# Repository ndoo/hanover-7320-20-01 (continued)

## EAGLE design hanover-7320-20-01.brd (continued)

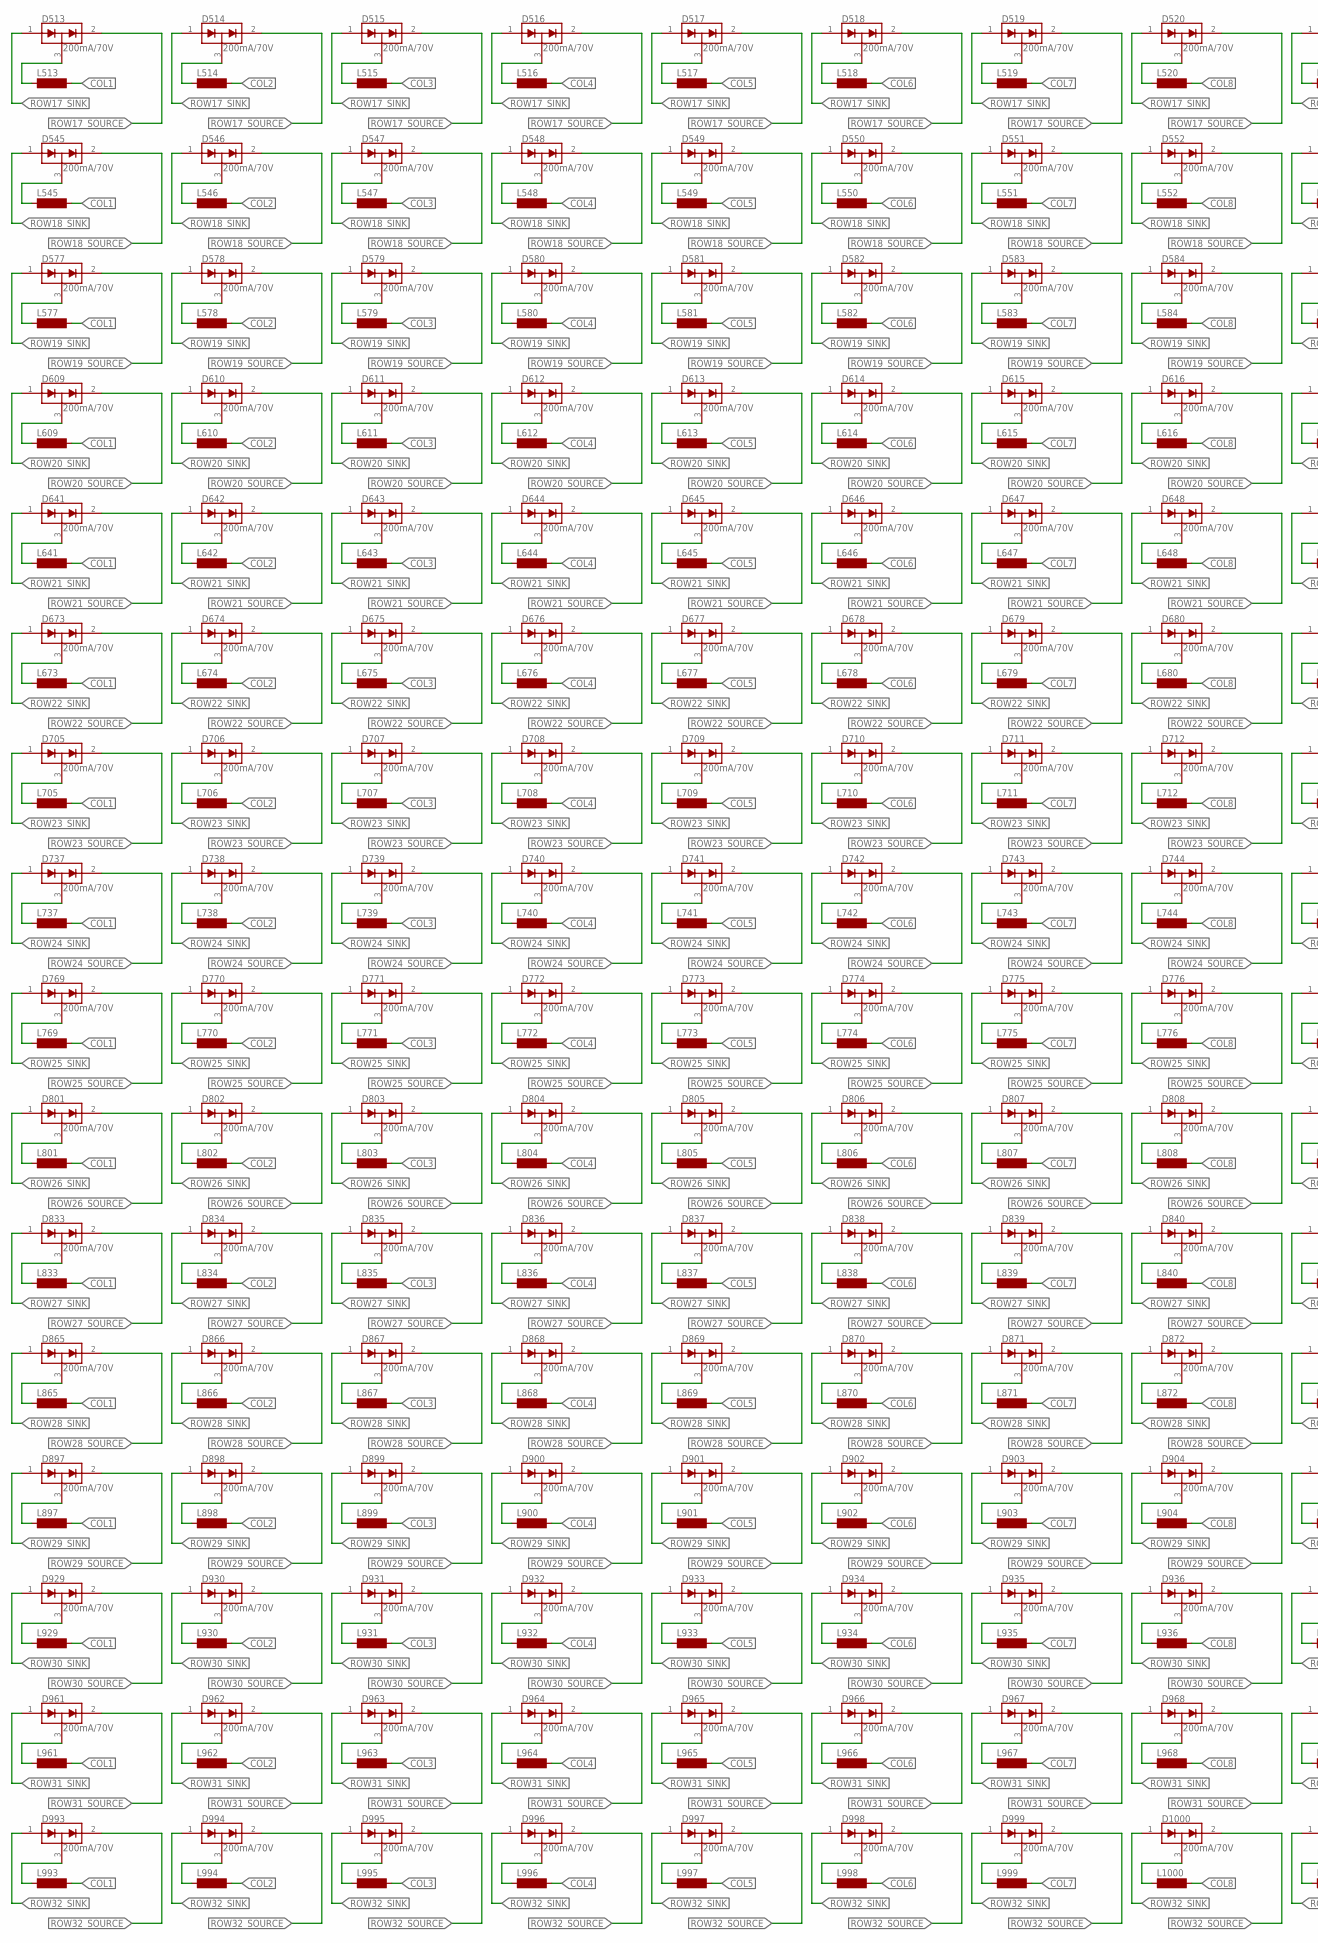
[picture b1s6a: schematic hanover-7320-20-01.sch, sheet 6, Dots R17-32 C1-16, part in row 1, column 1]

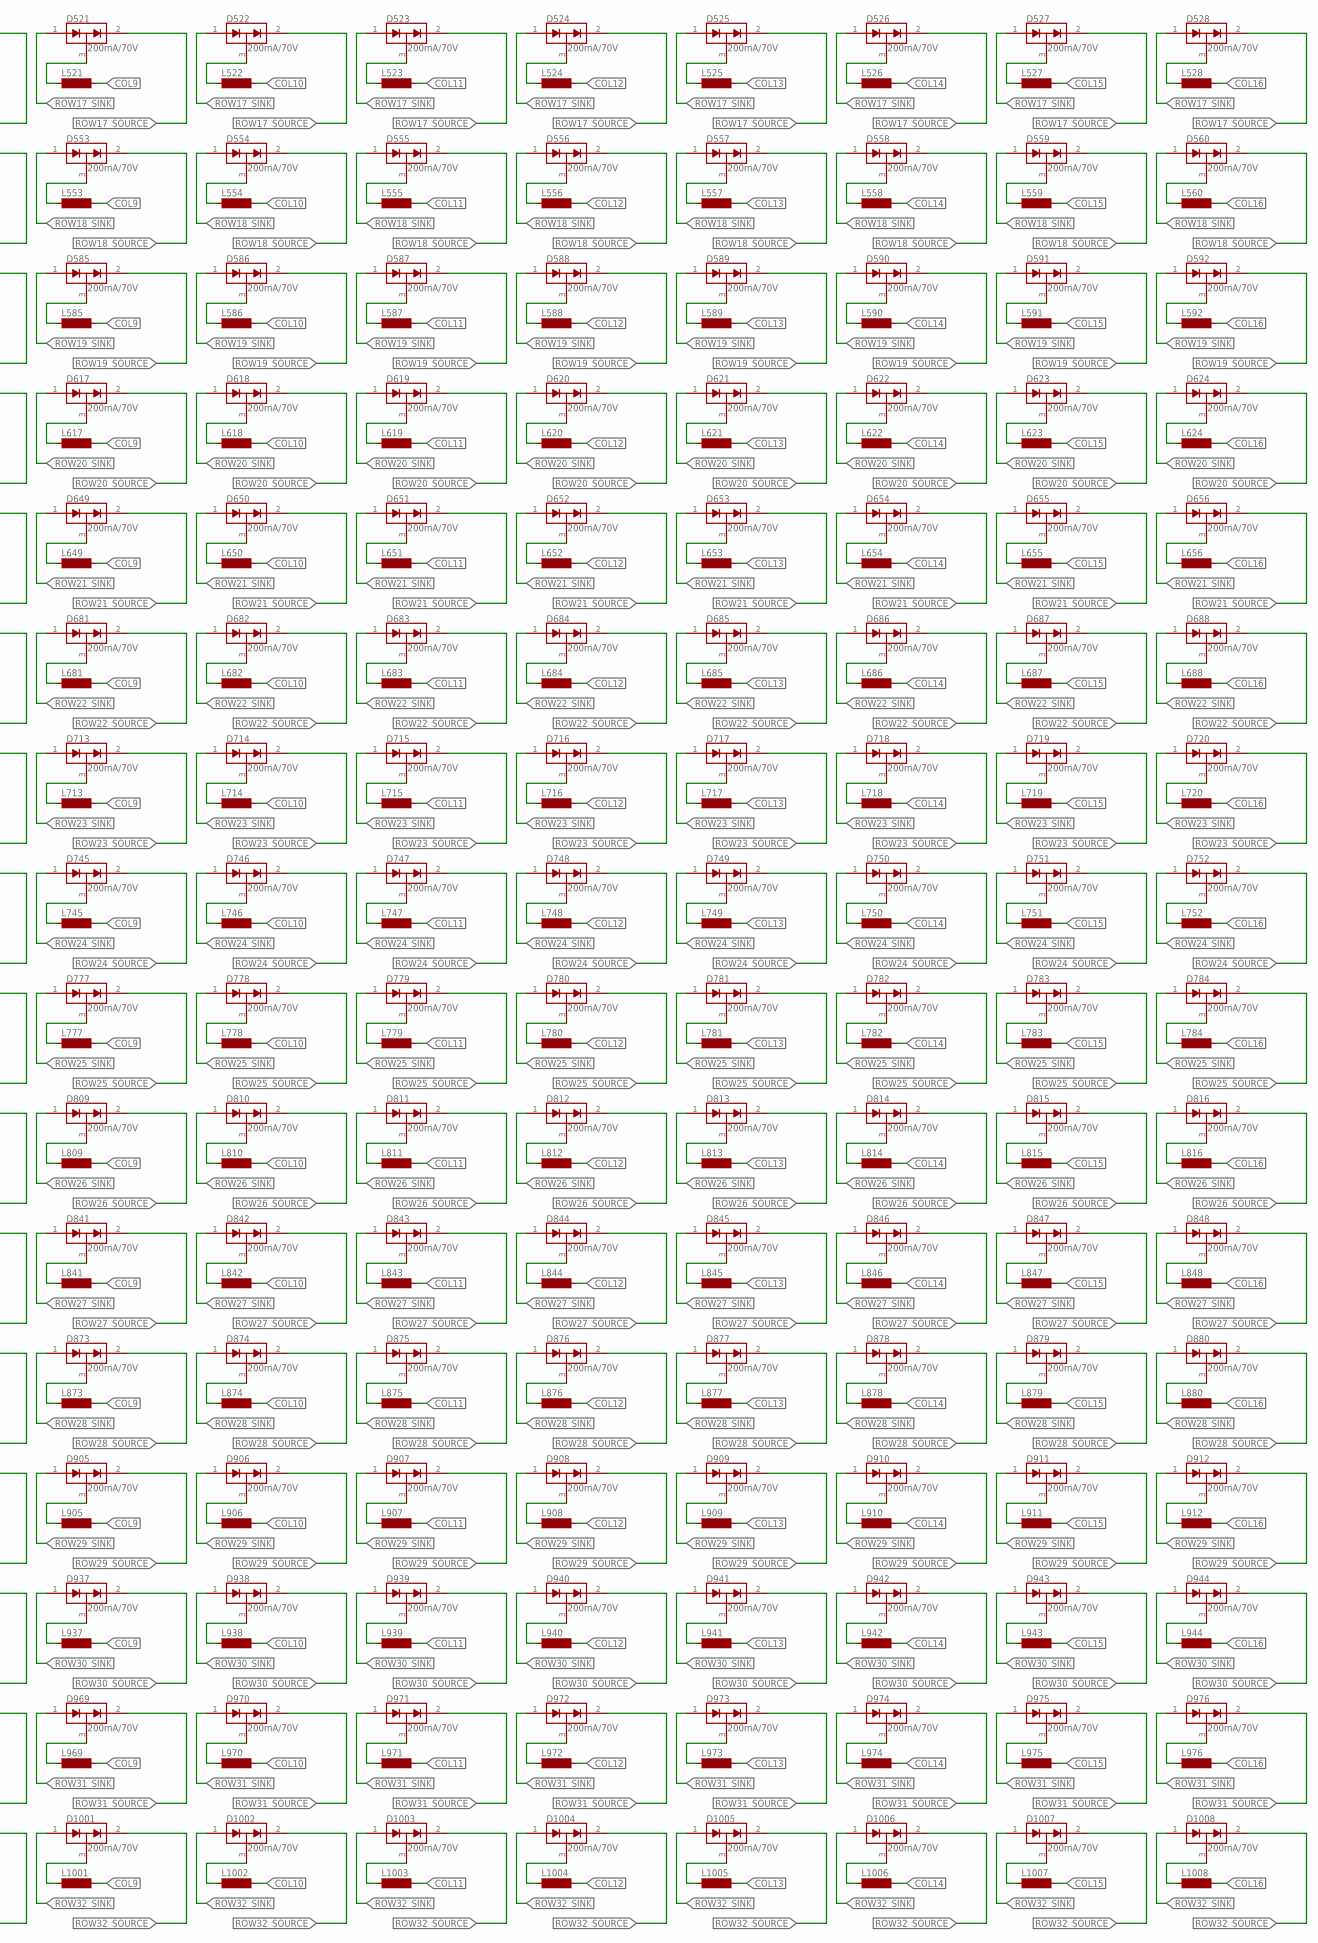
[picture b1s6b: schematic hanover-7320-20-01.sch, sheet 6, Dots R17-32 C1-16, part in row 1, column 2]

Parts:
D513, D514, D515, D516, D517, D518, D519, D520, D521, D522, D523, D524, D525, D526, D527, D528, D545, D546, D547, D548, D549, D550, D551, D552, D553, D554, D555, D556, D557, D558, D559, D560, D577, D578, D579, D580, D581, D582, D583, D584, D585, D586, D587, D588, D589, D590, D591, D592, D609, D610, D611, D612, D613, D614, D615, D616, D617, D618, D619, D620, D621, D622, D623, D624, D641, D642, D643, D644, D645, D646, D647, D648, D649, D650, D651, D652, D653, D654, D655, D656, D673, D674, D675, D676, D677, D678, D679, D680, D681, D682, D683, D684, D685, D686, D687, D688, D705, D706, D707, D708, D709, D710, D711, D712, D713, D714, D715, D716, D717, D718, D719, D720, D737, D738, D739, D740, D741, D742, D743, D744, D745, D746, D747, D748, D749, D750, D751, D752, D769, D770, D771, D772, D773, D774, D775, D776, D777, D778, D779, D780, D781, D782, D783, D784, D801, D802, D803, D804, D805, D806, D807, D808, D809, D810, D811, D812, D813, D814, D815, D816, D833, D834, D835, D836, D837, D838, D839, D840, D841, D842, D843, D844, D845, D846, D847, D848, D865, D866, D867, D868, D869, D870, D871, D872, D873, D874, D875, D876, D877, D878, D879, D880, D897, D898, D899, D900, D901, D902, D903, D904, D905, D906, D907, D908, D909, D910, D911, D912, D929, D930, D931, D932, D933, D934, D935, D936, D937, D938, D939, D940, D941, D942, D943, D944, D961, D962, D963, D964, D965, D966, D967, D968, D969, D970, D971, D972, D973, D974, D975, D976, D993, D994, D995, D996, D997, D998, D999, D1000, D1001, D1002, D1003, D1004, D1005, D1006, D1007, D1008: 200mA/70V; SOT23-3
L513, L514, L515, L516, L517, L518, L519, L520, L521, L522, L523, L524, L525, L526, L527, L528, L545, L546, L547, L548, L549, L550, L551, L552, L553, L554, L555, L556, L557, L558, L559, L560, L577, L578, L579, L580, L581, L582, L583, L584, L585, L586, L587, L588, L589, L590, L591, L592, L609, L610, L611, L612, L613, L614, L615, L616, L617, L618, L619, L620, L621, L622, L623, L624, L641, L642, L643, L644, L645, L646, L647, L648, L649, L650, L651, L652, L653, L654, L655, L656, L673, L674, L675, L676, L677, L678, L679, L680, L681, L682, L683, L684, L685, L686, L687, L688, L705, L706, L707, L708, L709, L710, L711, L712, L713, L714, L715, L716, L717, L718, L719, L720, L737, L738, L739, L740, L741, L742, L743, L744, L745, L746, L747, L748, L749, L750, L751, L752, L769, L770, L771, L772, L773, L774, L775, L776, L777, L778, L779, L780, L781, L782, L783, L784, L801, L802, L803, L804, L805, L806, L807, L808, L809, L810, L811, L812, L813, L814, L815, L816, L833, L834, L835, L836, L837, L838, L839, L840, L841, L842, L843, L844, L845, L846, L847, L848, L865, L866, L867, L868, L869, L870, L871, L872, L873, L874, L875, L876, L877, L878, L879, L880, L897, L898, L899, L900, L901, L902, L903, L904, L905, L906, L907, L908, L909, L910, L911, L912, L929, L930, L931, L932, L933, L934, L935, L936, L937, L938, L939, L940, L941, L942, L943, L944, L961, L962, L963, L964, L965, L966, L967, L968, L969, L970, L971, L972, L973, L974, L975, L976, L993, L994, L995, L996, L997, L998, L999, L1000, L1001, L1002, L1003, L1004, L1005, L1006, L1007, L1008: SD8

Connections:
COL1: L513.2, L545.2, L577.2, L609.2, L641.2, L673.2, L705.2, L737.2, L769.2, L801.2, L833.2, L865.2, L897.2, L929.2, L961.2, L993.2; also elsewhere on the board
COL2: L514.2, L546.2, L578.2, L610.2, L642.2, L674.2, L706.2, L738.2, L770.2, L802.2, L834.2, L866.2, L898.2, L930.2, L962.2, L994.2; also elsewhere on the board
COL3: L515.2, L547.2, L579.2, L611.2, L643.2, L675.2, L707.2, L739.2, L771.2, L803.2, L835.2, L867.2, L899.2, L931.2, L963.2, L995.2; also elsewhere on the board
COL4: L516.2, L548.2, L580.2, L612.2, L644.2, L676.2, L708.2, L740.2, L772.2, L804.2, L836.2, L868.2, L900.2, L932.2, L964.2, L996.2; also elsewhere on the board
COL5: L517.2, L549.2, L581.2, L613.2, L645.2, L677.2, L709.2, L741.2, L773.2, L805.2, L837.2, L869.2, L901.2, L933.2, L965.2, L997.2; also elsewhere on the board
COL6: L518.2, L550.2, L582.2, L614.2, L646.2, L678.2, L710.2, L742.2, L774.2, L806.2, L838.2, L870.2, L902.2, L934.2, L966.2, L998.2; also elsewhere on the board
COL7: L519.2, L551.2, L583.2, L615.2, L647.2, L679.2, L711.2, L743.2, L775.2, L807.2, L839.2, L871.2, L903.2, L935.2, L967.2, L999.2; also elsewhere on the board
COL8: L520.2, L552.2, L584.2, L616.2, L648.2, L680.2, L712.2, L744.2, L776.2, L808.2, L840.2, L872.2, L904.2, L936.2, L968.2, L1000.2; also elsewhere on the board
COL9: L521.2, L553.2, L585.2, L617.2, L649.2, L681.2, L713.2, L745.2, L777.2, L809.2, L841.2, L873.2, L905.2, L937.2, L969.2, L1001.2; also elsewhere on the board
COL10: L522.2, L554.2, L586.2, L618.2, L650.2, L682.2, L714.2, L746.2, L778.2, L810.2, L842.2, L874.2, L906.2, L938.2, L970.2, L1002.2; also elsewhere on the board
COL11: L523.2, L555.2, L587.2, L619.2, L651.2, L683.2, L715.2, L747.2, L779.2, L811.2, L843.2, L875.2, L907.2, L939.2, L971.2, L1003.2; also elsewhere on the board
COL12: L524.2, L556.2, L588.2, L620.2, L652.2, L684.2, L716.2, L748.2, L780.2, L812.2, L844.2, L876.2, L908.2, L940.2, L972.2, L1004.2; also elsewhere on the board
COL13: L525.2, L557.2, L589.2, L621.2, L653.2, L685.2, L717.2, L749.2, L781.2, L813.2, L845.2, L877.2, L909.2, L941.2, L973.2, L1005.2; also elsewhere on the board
COL14: L526.2, L558.2, L590.2, L622.2, L654.2, L686.2, L718.2, L750.2, L782.2, L814.2, L846.2, L878.2, L910.2, L942.2, L974.2, L1006.2; also elsewhere on the board
COL15: L527.2, L559.2, L591.2, L623.2, L655.2, L687.2, L719.2, L751.2, L783.2, L815.2, L847.2, L879.2, L911.2, L943.2, L975.2, L1007.2; also elsewhere on the board
COL16: L528.2, L560.2, L592.2, L624.2, L656.2, L688.2, L720.2, L752.2, L784.2, L816.2, L848.2, L880.2, L912.2, L944.2, L976.2, L1008.2; also elsewhere on the board
unnamed: D513.3 (COM), L513.1
unnamed: D514.3 (COM), L514.1
unnamed: D515.3 (COM), L515.1
unnamed: D516.3 (COM), L516.1
unnamed: D517.3 (COM), L517.1
unnamed: D518.3 (COM), L518.1
unnamed: D519.3 (COM), L519.1
unnamed: D520.3 (COM), L520.1
unnamed: D521.3 (COM), L521.1
unnamed: D522.3 (COM), L522.1
unnamed: D523.3 (COM), L523.1
unnamed: D524.3 (COM), L524.1
unnamed: D525.3 (COM), L525.1
unnamed: D526.3 (COM), L526.1
unnamed: D527.3 (COM), L527.1
unnamed: D528.3 (COM), L528.1
unnamed: D545.3 (COM), L545.1
unnamed: D546.3 (COM), L546.1
unnamed: D547.3 (COM), L547.1
unnamed: D548.3 (COM), L548.1
unnamed: D549.3 (COM), L549.1
unnamed: D550.3 (COM), L550.1
unnamed: D551.3 (COM), L551.1
unnamed: D552.3 (COM), L552.1
unnamed: D553.3 (COM), L553.1
unnamed: D554.3 (COM), L554.1
unnamed: D555.3 (COM), L555.1
unnamed: D556.3 (COM), L556.1
unnamed: D557.3 (COM), L557.1
unnamed: D558.3 (COM), L558.1
unnamed: D559.3 (COM), L559.1
unnamed: D560.3 (COM), L560.1
unnamed: D577.3 (COM), L577.1
unnamed: D578.3 (COM), L578.1
unnamed: D579.3 (COM), L579.1
unnamed: D580.3 (COM), L580.1
unnamed: D581.3 (COM), L581.1
unnamed: D582.3 (COM), L582.1
unnamed: D583.3 (COM), L583.1
unnamed: D584.3 (COM), L584.1
unnamed: D585.3 (COM), L585.1
unnamed: D586.3 (COM), L586.1
unnamed: D587.3 (COM), L587.1
unnamed: D588.3 (COM), L588.1
unnamed: D589.3 (COM), L589.1
unnamed: D590.3 (COM), L590.1
unnamed: D591.3 (COM), L591.1
unnamed: D592.3 (COM), L592.1
unnamed: D609.3 (COM), L609.1
unnamed: D610.3 (COM), L610.1
unnamed: D611.3 (COM), L611.1
unnamed: D612.3 (COM), L612.1
unnamed: D613.3 (COM), L613.1
unnamed: D614.3 (COM), L614.1
unnamed: D615.3 (COM), L615.1
unnamed: D616.3 (COM), L616.1
unnamed: D617.3 (COM), L617.1
unnamed: D618.3 (COM), L618.1
unnamed: D619.3 (COM), L619.1
unnamed: D620.3 (COM), L620.1
unnamed: D621.3 (COM), L621.1
unnamed: D622.3 (COM), L622.1
unnamed: D623.3 (COM), L623.1
unnamed: D624.3 (COM), L624.1
unnamed: D641.3 (COM), L641.1
unnamed: D642.3 (COM), L642.1
unnamed: D643.3 (COM), L643.1
unnamed: D644.3 (COM), L644.1
unnamed: D645.3 (COM), L645.1
unnamed: D646.3 (COM), L646.1
unnamed: D647.3 (COM), L647.1
unnamed: D648.3 (COM), L648.1
unnamed: D649.3 (COM), L649.1
unnamed: D650.3 (COM), L650.1
unnamed: D651.3 (COM), L651.1
unnamed: D652.3 (COM), L652.1
unnamed: D653.3 (COM), L653.1
unnamed: D654.3 (COM), L654.1
unnamed: D655.3 (COM), L655.1
unnamed: D656.3 (COM), L656.1
unnamed: D673.3 (COM), L673.1
unnamed: D674.3 (COM), L674.1
unnamed: D675.3 (COM), L675.1
unnamed: D676.3 (COM), L676.1
unnamed: D677.3 (COM), L677.1
unnamed: D678.3 (COM), L678.1
unnamed: D679.3 (COM), L679.1
unnamed: D680.3 (COM), L680.1
unnamed: D681.3 (COM), L681.1
unnamed: D682.3 (COM), L682.1
unnamed: D683.3 (COM), L683.1
unnamed: D684.3 (COM), L684.1
unnamed: D685.3 (COM), L685.1
unnamed: D686.3 (COM), L686.1
unnamed: D687.3 (COM), L687.1
unnamed: D688.3 (COM), L688.1
unnamed: D705.3 (COM), L705.1
unnamed: D706.3 (COM), L706.1
unnamed: D707.3 (COM), L707.1
unnamed: D708.3 (COM), L708.1
unnamed: D709.3 (COM), L709.1
unnamed: D710.3 (COM), L710.1
unnamed: D711.3 (COM), L711.1
unnamed: D712.3 (COM), L712.1
unnamed: D713.3 (COM), L713.1
unnamed: D714.3 (COM), L714.1
unnamed: D715.3 (COM), L715.1
unnamed: D716.3 (COM), L716.1
unnamed: D717.3 (COM), L717.1
unnamed: D718.3 (COM), L718.1
unnamed: D719.3 (COM), L719.1
unnamed: D720.3 (COM), L720.1
unnamed: D737.3 (COM), L737.1
unnamed: D738.3 (COM), L738.1
unnamed: D739.3 (COM), L739.1
unnamed: D740.3 (COM), L740.1
unnamed: D741.3 (COM), L741.1
unnamed: D742.3 (COM), L742.1
unnamed: D743.3 (COM), L743.1
unnamed: D744.3 (COM), L744.1
unnamed: D745.3 (COM), L745.1
unnamed: D746.3 (COM), L746.1
unnamed: D747.3 (COM), L747.1
unnamed: D748.3 (COM), L748.1
unnamed: D749.3 (COM), L749.1
unnamed: D750.3 (COM), L750.1
unnamed: D751.3 (COM), L751.1
unnamed: D752.3 (COM), L752.1
unnamed: D769.3 (COM), L769.1
unnamed: D770.3 (COM), L770.1
unnamed: D771.3 (COM), L771.1
unnamed: D772.3 (COM), L772.1
unnamed: D773.3 (COM), L773.1
unnamed: D774.3 (COM), L774.1
unnamed: D775.3 (COM), L775.1
unnamed: D776.3 (COM), L776.1
unnamed: D777.3 (COM), L777.1
unnamed: D778.3 (COM), L778.1
unnamed: D779.3 (COM), L779.1
unnamed: D780.3 (COM), L780.1
unnamed: D781.3 (COM), L781.1
unnamed: D782.3 (COM), L782.1
unnamed: D783.3 (COM), L783.1
unnamed: D784.3 (COM), L784.1
unnamed: D801.3 (COM), L801.1
unnamed: D802.3 (COM), L802.1
unnamed: D803.3 (COM), L803.1
unnamed: D804.3 (COM), L804.1
unnamed: D805.3 (COM), L805.1
unnamed: D806.3 (COM), L806.1
unnamed: D807.3 (COM), L807.1
unnamed: D808.3 (COM), L808.1
unnamed: D809.3 (COM), L809.1
unnamed: D810.3 (COM), L810.1
unnamed: D811.3 (COM), L811.1
unnamed: D812.3 (COM), L812.1
unnamed: D813.3 (COM), L813.1
unnamed: D814.3 (COM), L814.1
unnamed: D815.3 (COM), L815.1
unnamed: D816.3 (COM), L816.1
unnamed: D833.3 (COM), L833.1
unnamed: D834.3 (COM), L834.1
unnamed: D835.3 (COM), L835.1
unnamed: D836.3 (COM), L836.1
unnamed: D837.3 (COM), L837.1
unnamed: D838.3 (COM), L838.1
unnamed: D839.3 (COM), L839.1
unnamed: D840.3 (COM), L840.1
unnamed: D841.3 (COM), L841.1
unnamed: D842.3 (COM), L842.1
unnamed: D843.3 (COM), L843.1
unnamed: D844.3 (COM), L844.1
unnamed: D845.3 (COM), L845.1
unnamed: D846.3 (COM), L846.1
unnamed: D847.3 (COM), L847.1
unnamed: D848.3 (COM), L848.1
unnamed: D865.3 (COM), L865.1
unnamed: D866.3 (COM), L866.1
unnamed: D867.3 (COM), L867.1
unnamed: D868.3 (COM), L868.1
unnamed: D869.3 (COM), L869.1
unnamed: D870.3 (COM), L870.1
unnamed: D871.3 (COM), L871.1
unnamed: D872.3 (COM), L872.1
unnamed: D873.3 (COM), L873.1
unnamed: D874.3 (COM), L874.1
unnamed: D875.3 (COM), L875.1
unnamed: D876.3 (COM), L876.1
unnamed: D877.3 (COM), L877.1
unnamed: D878.3 (COM), L878.1
unnamed: D879.3 (COM), L879.1
unnamed: D880.3 (COM), L880.1
unnamed: D897.3 (COM), L897.1
unnamed: D898.3 (COM), L898.1
unnamed: D899.3 (COM), L899.1
unnamed: D900.3 (COM), L900.1
unnamed: D901.3 (COM), L901.1
unnamed: D902.3 (COM), L902.1
unnamed: D903.3 (COM), L903.1
unnamed: D904.3 (COM), L904.1
unnamed: D905.3 (COM), L905.1
unnamed: D906.3 (COM), L906.1
unnamed: D907.3 (COM), L907.1
unnamed: D908.3 (COM), L908.1
unnamed: D909.3 (COM), L909.1
unnamed: D910.3 (COM), L910.1
unnamed: D911.3 (COM), L911.1
unnamed: D912.3 (COM), L912.1
unnamed: D929.3 (COM), L929.1
unnamed: D930.3 (COM), L930.1
unnamed: D931.3 (COM), L931.1
unnamed: D932.3 (COM), L932.1
unnamed: D933.3 (COM), L933.1
unnamed: D934.3 (COM), L934.1
unnamed: D935.3 (COM), L935.1
unnamed: D936.3 (COM), L936.1
unnamed: D937.3 (COM), L937.1
unnamed: D938.3 (COM), L938.1
unnamed: D939.3 (COM), L939.1
unnamed: D940.3 (COM), L940.1
unnamed: D941.3 (COM), L941.1
unnamed: D942.3 (COM), L942.1
unnamed: D943.3 (COM), L943.1
unnamed: D944.3 (COM), L944.1
unnamed: D961.3 (COM), L961.1
unnamed: D962.3 (COM), L962.1
unnamed: D963.3 (COM), L963.1
unnamed: D964.3 (COM), L964.1
unnamed: D965.3 (COM), L965.1
unnamed: D966.3 (COM), L966.1
unnamed: D967.3 (COM), L967.1
unnamed: D968.3 (COM), L968.1
unnamed: D969.3 (COM), L969.1
unnamed: D970.3 (COM), L970.1
unnamed: D971.3 (COM), L971.1
unnamed: D972.3 (COM), L972.1
unnamed: D973.3 (COM), L973.1
unnamed: D974.3 (COM), L974.1
unnamed: D975.3 (COM), L975.1
unnamed: D976.3 (COM), L976.1
unnamed: D993.3 (COM), L993.1
unnamed: D994.3 (COM), L994.1
unnamed: D995.3 (COM), L995.1
unnamed: D996.3 (COM), L996.1
unnamed: D997.3 (COM), L997.1
unnamed: D998.3 (COM), L998.1
unnamed: D999.3 (COM), L999.1
unnamed: D1000.3 (COM), L1000.1
unnamed: D1001.3 (COM), L1001.1
unnamed: D1002.3 (COM), L1002.1
unnamed: D1003.3 (COM), L1003.1
unnamed: D1004.3 (COM), L1004.1
unnamed: D1005.3 (COM), L1005.1
unnamed: D1006.3 (COM), L1006.1
unnamed: D1007.3 (COM), L1007.1
unnamed: D1008.3 (COM), L1008.1
ROW17_SINK: D513.1 (A1), D514.1 (A1), D515.1 (A1), D516.1 (A1), D517.1 (A1), D518.1 (A1), D519.1 (A1), D520.1 (A1), D521.1 (A1), D522.1 (A1), D523.1 (A1), D524.1 (A1), D525.1 (A1), D526.1 (A1), D527.1 (A1), D528.1 (A1); also elsewhere on the board
ROW17_SOURCE: D513.2 (C2), D514.2 (C2), D515.2 (C2), D516.2 (C2), D517.2 (C2), D518.2 (C2), D519.2 (C2), D520.2 (C2), D521.2 (C2), D522.2 (C2), D523.2 (C2), D524.2 (C2), D525.2 (C2), D526.2 (C2), D527.2 (C2), D528.2 (C2); also elsewhere on the board
ROW18_SINK: D545.1 (A1), D546.1 (A1), D547.1 (A1), D548.1 (A1), D549.1 (A1), D550.1 (A1), D551.1 (A1), D552.1 (A1), D553.1 (A1), D554.1 (A1), D555.1 (A1), D556.1 (A1), D557.1 (A1), D558.1 (A1), D559.1 (A1), D560.1 (A1); also elsewhere on the board
ROW18_SOURCE: D545.2 (C2), D546.2 (C2), D547.2 (C2), D548.2 (C2), D549.2 (C2), D550.2 (C2), D551.2 (C2), D552.2 (C2), D553.2 (C2), D554.2 (C2), D555.2 (C2), D556.2 (C2), D557.2 (C2), D558.2 (C2), D559.2 (C2), D560.2 (C2); also elsewhere on the board
ROW19_SINK: D577.1 (A1), D578.1 (A1), D579.1 (A1), D580.1 (A1), D581.1 (A1), D582.1 (A1), D583.1 (A1), D584.1 (A1), D585.1 (A1), D586.1 (A1), D587.1 (A1), D588.1 (A1), D589.1 (A1), D590.1 (A1), D591.1 (A1), D592.1 (A1); also elsewhere on the board
ROW19_SOURCE: D577.2 (C2), D578.2 (C2), D579.2 (C2), D580.2 (C2), D581.2 (C2), D582.2 (C2), D583.2 (C2), D584.2 (C2), D585.2 (C2), D586.2 (C2), D587.2 (C2), D588.2 (C2), D589.2 (C2), D590.2 (C2), D591.2 (C2), D592.2 (C2); also elsewhere on the board
ROW20_SINK: D609.1 (A1), D610.1 (A1), D611.1 (A1), D612.1 (A1), D613.1 (A1), D614.1 (A1), D615.1 (A1), D616.1 (A1), D617.1 (A1), D618.1 (A1), D619.1 (A1), D620.1 (A1), D621.1 (A1), D622.1 (A1), D623.1 (A1), D624.1 (A1); also elsewhere on the board
ROW20_SOURCE: D609.2 (C2), D610.2 (C2), D611.2 (C2), D612.2 (C2), D613.2 (C2), D614.2 (C2), D615.2 (C2), D616.2 (C2), D617.2 (C2), D618.2 (C2), D619.2 (C2), D620.2 (C2), D621.2 (C2), D622.2 (C2), D623.2 (C2), D624.2 (C2); also elsewhere on the board
ROW21_SINK: D641.1 (A1), D642.1 (A1), D643.1 (A1), D644.1 (A1), D645.1 (A1), D646.1 (A1), D647.1 (A1), D648.1 (A1), D649.1 (A1), D650.1 (A1), D651.1 (A1), D652.1 (A1), D653.1 (A1), D654.1 (A1), D655.1 (A1), D656.1 (A1); also elsewhere on the board
ROW21_SOURCE: D641.2 (C2), D642.2 (C2), D643.2 (C2), D644.2 (C2), D645.2 (C2), D646.2 (C2), D647.2 (C2), D648.2 (C2), D649.2 (C2), D650.2 (C2), D651.2 (C2), D652.2 (C2), D653.2 (C2), D654.2 (C2), D655.2 (C2), D656.2 (C2); also elsewhere on the board
ROW22_SINK: D673.1 (A1), D674.1 (A1), D675.1 (A1), D676.1 (A1), D677.1 (A1), D678.1 (A1), D679.1 (A1), D680.1 (A1), D681.1 (A1), D682.1 (A1), D683.1 (A1), D684.1 (A1), D685.1 (A1), D686.1 (A1), D687.1 (A1), D688.1 (A1); also elsewhere on the board
ROW22_SOURCE: D673.2 (C2), D674.2 (C2), D675.2 (C2), D676.2 (C2), D677.2 (C2), D678.2 (C2), D679.2 (C2), D680.2 (C2), D681.2 (C2), D682.2 (C2), D683.2 (C2), D684.2 (C2), D685.2 (C2), D686.2 (C2), D687.2 (C2), D688.2 (C2); also elsewhere on the board
ROW23_SINK: D705.1 (A1), D706.1 (A1), D707.1 (A1), D708.1 (A1), D709.1 (A1), D710.1 (A1), D711.1 (A1), D712.1 (A1), D713.1 (A1), D714.1 (A1), D715.1 (A1), D716.1 (A1), D717.1 (A1), D718.1 (A1), D719.1 (A1), D720.1 (A1); also elsewhere on the board
ROW23_SOURCE: D705.2 (C2), D706.2 (C2), D707.2 (C2), D708.2 (C2), D709.2 (C2), D710.2 (C2), D711.2 (C2), D712.2 (C2), D713.2 (C2), D714.2 (C2), D715.2 (C2), D716.2 (C2), D717.2 (C2), D718.2 (C2), D719.2 (C2), D720.2 (C2); also elsewhere on the board
ROW24_SINK: D737.1 (A1), D738.1 (A1), D739.1 (A1), D740.1 (A1), D741.1 (A1), D742.1 (A1), D743.1 (A1), D744.1 (A1), D745.1 (A1), D746.1 (A1), D747.1 (A1), D748.1 (A1), D749.1 (A1), D750.1 (A1), D751.1 (A1), D752.1 (A1); also elsewhere on the board
ROW24_SOURCE: D737.2 (C2), D738.2 (C2), D739.2 (C2), D740.2 (C2), D741.2 (C2), D742.2 (C2), D743.2 (C2), D744.2 (C2), D745.2 (C2), D746.2 (C2), D747.2 (C2), D748.2 (C2), D749.2 (C2), D750.2 (C2), D751.2 (C2), D752.2 (C2); also elsewhere on the board
ROW25_SINK: D769.1 (A1), D770.1 (A1), D771.1 (A1), D772.1 (A1), D773.1 (A1), D774.1 (A1), D775.1 (A1), D776.1 (A1), D777.1 (A1), D778.1 (A1), D779.1 (A1), D780.1 (A1), D781.1 (A1), D782.1 (A1), D783.1 (A1), D784.1 (A1); also elsewhere on the board
ROW25_SOURCE: D769.2 (C2), D770.2 (C2), D771.2 (C2), D772.2 (C2), D773.2 (C2), D774.2 (C2), D775.2 (C2), D776.2 (C2), D777.2 (C2), D778.2 (C2), D779.2 (C2), D780.2 (C2), D781.2 (C2), D782.2 (C2), D783.2 (C2), D784.2 (C2); also elsewhere on the board
ROW26_SINK: D801.1 (A1), D802.1 (A1), D803.1 (A1), D804.1 (A1), D805.1 (A1), D806.1 (A1), D807.1 (A1), D808.1 (A1), D809.1 (A1), D810.1 (A1), D811.1 (A1), D812.1 (A1), D813.1 (A1), D814.1 (A1), D815.1 (A1), D816.1 (A1); also elsewhere on the board
ROW26_SOURCE: D801.2 (C2), D802.2 (C2), D803.2 (C2), D804.2 (C2), D805.2 (C2), D806.2 (C2), D807.2 (C2), D808.2 (C2), D809.2 (C2), D810.2 (C2), D811.2 (C2), D812.2 (C2), D813.2 (C2), D814.2 (C2), D815.2 (C2), D816.2 (C2); also elsewhere on the board
ROW27_SINK: D833.1 (A1), D834.1 (A1), D835.1 (A1), D836.1 (A1), D837.1 (A1), D838.1 (A1), D839.1 (A1), D840.1 (A1), D841.1 (A1), D842.1 (A1), D843.1 (A1), D844.1 (A1), D845.1 (A1), D846.1 (A1), D847.1 (A1), D848.1 (A1); also elsewhere on the board
ROW27_SOURCE: D833.2 (C2), D834.2 (C2), D835.2 (C2), D836.2 (C2), D837.2 (C2), D838.2 (C2), D839.2 (C2), D840.2 (C2), D841.2 (C2), D842.2 (C2), D843.2 (C2), D844.2 (C2), D845.2 (C2), D846.2 (C2), D847.2 (C2), D848.2 (C2); also elsewhere on the board
ROW28_SINK: D865.1 (A1), D866.1 (A1), D867.1 (A1), D868.1 (A1), D869.1 (A1), D870.1 (A1), D871.1 (A1), D872.1 (A1), D873.1 (A1), D874.1 (A1), D875.1 (A1), D876.1 (A1), D877.1 (A1), D878.1 (A1), D879.1 (A1), D880.1 (A1); also elsewhere on the board
ROW28_SOURCE: D865.2 (C2), D866.2 (C2), D867.2 (C2), D868.2 (C2), D869.2 (C2), D870.2 (C2), D871.2 (C2), D872.2 (C2), D873.2 (C2), D874.2 (C2), D875.2 (C2), D876.2 (C2), D877.2 (C2), D878.2 (C2), D879.2 (C2), D880.2 (C2); also elsewhere on the board
ROW29_SINK: D897.1 (A1), D898.1 (A1), D899.1 (A1), D900.1 (A1), D901.1 (A1), D902.1 (A1), D903.1 (A1), D904.1 (A1), D905.1 (A1), D906.1 (A1), D907.1 (A1), D908.1 (A1), D909.1 (A1), D910.1 (A1), D911.1 (A1), D912.1 (A1); also elsewhere on the board
ROW29_SOURCE: D897.2 (C2), D898.2 (C2), D899.2 (C2), D900.2 (C2), D901.2 (C2), D902.2 (C2), D903.2 (C2), D904.2 (C2), D905.2 (C2), D906.2 (C2), D907.2 (C2), D908.2 (C2), D909.2 (C2), D910.2 (C2), D911.2 (C2), D912.2 (C2); also elsewhere on the board
ROW30_SINK: D929.1 (A1), D930.1 (A1), D931.1 (A1), D932.1 (A1), D933.1 (A1), D934.1 (A1), D935.1 (A1), D936.1 (A1), D937.1 (A1), D938.1 (A1), D939.1 (A1), D940.1 (A1), D941.1 (A1), D942.1 (A1), D943.1 (A1), D944.1 (A1); also elsewhere on the board
ROW30_SOURCE: D929.2 (C2), D930.2 (C2), D931.2 (C2), D932.2 (C2), D933.2 (C2), D934.2 (C2), D935.2 (C2), D936.2 (C2), D937.2 (C2), D938.2 (C2), D939.2 (C2), D940.2 (C2), D941.2 (C2), D942.2 (C2), D943.2 (C2), D944.2 (C2); also elsewhere on the board
ROW31_SINK: D961.1 (A1), D962.1 (A1), D963.1 (A1), D964.1 (A1), D965.1 (A1), D966.1 (A1), D967.1 (A1), D968.1 (A1), D969.1 (A1), D970.1 (A1), D971.1 (A1), D972.1 (A1), D973.1 (A1), D974.1 (A1), D975.1 (A1), D976.1 (A1); also elsewhere on the board
ROW31_SOURCE: D961.2 (C2), D962.2 (C2), D963.2 (C2), D964.2 (C2), D965.2 (C2), D966.2 (C2), D967.2 (C2), D968.2 (C2), D969.2 (C2), D970.2 (C2), D971.2 (C2), D972.2 (C2), D973.2 (C2), D974.2 (C2), D975.2 (C2), D976.2 (C2); also elsewhere on the board
ROW32_SINK: D993.1 (A1), D994.1 (A1), D995.1 (A1), D996.1 (A1), D997.1 (A1), D998.1 (A1), D999.1 (A1), D1000.1 (A1), D1001.1 (A1), D1002.1 (A1), D1003.1 (A1), D1004.1 (A1), D1005.1 (A1), D1006.1 (A1), D1007.1 (A1), D1008.1 (A1); also elsewhere on the board
ROW32_SOURCE: D993.2 (C2), D994.2 (C2), D995.2 (C2), D996.2 (C2), D997.2 (C2), D998.2 (C2), D999.2 (C2), D1000.2 (C2), D1001.2 (C2), D1002.2 (C2), D1003.2 (C2), D1004.2 (C2), D1005.2 (C2), D1006.2 (C2), D1007.2 (C2), D1008.2 (C2); also elsewhere on the board
